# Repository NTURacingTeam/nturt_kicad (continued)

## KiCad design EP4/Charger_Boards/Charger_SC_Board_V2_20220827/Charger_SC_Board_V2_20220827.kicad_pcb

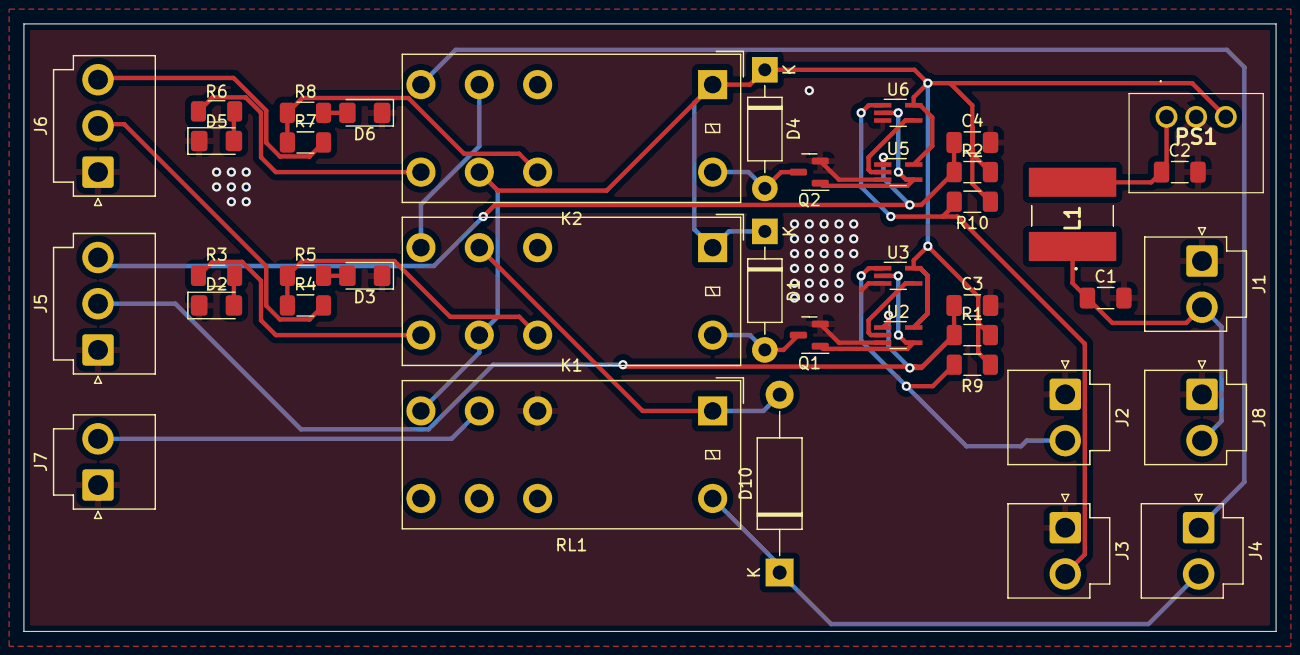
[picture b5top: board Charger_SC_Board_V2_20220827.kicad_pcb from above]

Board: 2 copper layers, 107.3 x 52.1 mm, 40 parts (0 on the bottom side), 29 nets.

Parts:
C1, C3, C4: 10u; C_1206_3216Metric_Pad1.33x1.80mm_HandSolder
C2: 2.2u; C_1206_3216Metric_Pad1.33x1.80mm_HandSolder
D1, D4: 1N4001; D_DO-41_SOD81_P10.16mm_Horizontal
D2, D5: GREEN; D_1206_3216Metric_Pad1.42x1.75mm_HandSolder
D3, D6: RED; D_1206_3216Metric_Pad1.42x1.75mm_HandSolder
D10: D_TVS; D_DO-15_P15.24mm_Horizontal
J1: PWR; JST_VH_B2P-VH-B_1x02_P3.96mm_Vertical
J2: IMD; JST_VH_B2P-VH-B_1x02_P3.96mm_Vertical
J3: BMS; JST_VH_B2P-VH-B_1x02_P3.96mm_Vertical
J4: SC; JST_VH_B2P-VH-B_1x02_P3.96mm_Vertical
J5: Buttons; JST_VH_B3P-VH-B_1x03_P3.96mm_Vertical
J6: Button_LED; JST_VH_B3P-VH-B_1x03_P3.96mm_Vertical
J7: Charger_Control; JST_VH_B2P-VH-B_1x02_P3.96mm_Vertical
J8: HV_PWR; JST_VH_B2P-VH-B_1x02_P3.96mm_Vertical
K1, K2: G2RL-24-DC5; Relay_DPDT_Omron_G2RL
L1: 68u; RLS686
PS1: R-78E5.0-1.0; R78B5020
Q1, Q2: 2N7002; SOT-23
R1, R2, R9, R10: 10K; R_1206_3216Metric_Pad1.30x1.75mm_HandSolder
R3, R5, R6, R8: 680; R_1206_3216Metric_Pad1.30x1.75mm_HandSolder
R4, R7: 100; R_1206_3216Metric_Pad1.30x1.75mm_HandSolder
RL1: G2RL-24-DC5; Relay_DPDT_Omron_G2RL
U2, U3, U5, U6: 74AHC1G00; SOT-353_SC-70-5_Handsoldering

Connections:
+5V: D1.1 (K), D4.1 (K), K1.1, K1.6, K2.1, K2.6, PS1.3 (+VOUT), R1.2, R2.2, R9.1, R10.1, RL1.4, U2.5 (VCC), U3.5 (VCC), U5.5 (VCC), U6.5 (VCC)
+24V: C1.1, J1.2, J8.2, L1.1
/+VCC: C2.1, L1.2, PS1.1 (+VIN)
/BMS_Latch/Latch_Out: Q2.1 (G), U5.4, U6.2
/BMS_Relay_Control/SC_In: K1.4, K2.3
/IMD_Latch/Latch_Out: Q1.1 (G), U2.4, U3.2
BMS_Button: C4.1, J5.3, R2.1, U5.1
BMS_Button_LED: J6.3, R7.2
BMS_Fault: J3.2, R10.2, U6.1
Charger: J7.2, RL1.3
GND: C1.2, C2.2, C3.2, C4.2, D2.1 (K), D3.1 (K), D5.1 (K), D6.1 (K), J1.1, J2.1, J3.1, J5.1, J6.1, J7.1, J8.1, PS1.2 (GND), Q1.2 (S), Q2.2 (S), RL1.2, U2.3 (GND), U3.3 (GND), U5.3 (GND), U6.3 (GND)
IMD_Button: C3.1, J5.2, R1.1, U2.1
IMD_Button_LED: J6.2, R4.2
IMD_Fault: J2.2, R9.2, U3.1
unnamed: D1.2 (A), K1.8, Q1.3 (D)
unnamed: D2.2 (A), R3.2
unnamed: D3.2 (A), R5.2
unnamed: D4.2 (A), K2.8, Q2.3 (D)
unnamed: D5.2 (A), R6.2
unnamed: D6.2 (A), R8.2
unnamed: K1.5, R3.1
unnamed: K1.7, R4.1, R5.1
unnamed: K2.5, R6.1
unnamed: K2.7, R7.1, R8.1
unnamed: U2.2, U3.4
unnamed: U5.2, U6.4
SC_In: D10.1 (A1), J4.2, RL1.8
SC_Out: J4.1, K2.4
SC_Relay_Out: D10.2 (A2), K1.3, RL1.1

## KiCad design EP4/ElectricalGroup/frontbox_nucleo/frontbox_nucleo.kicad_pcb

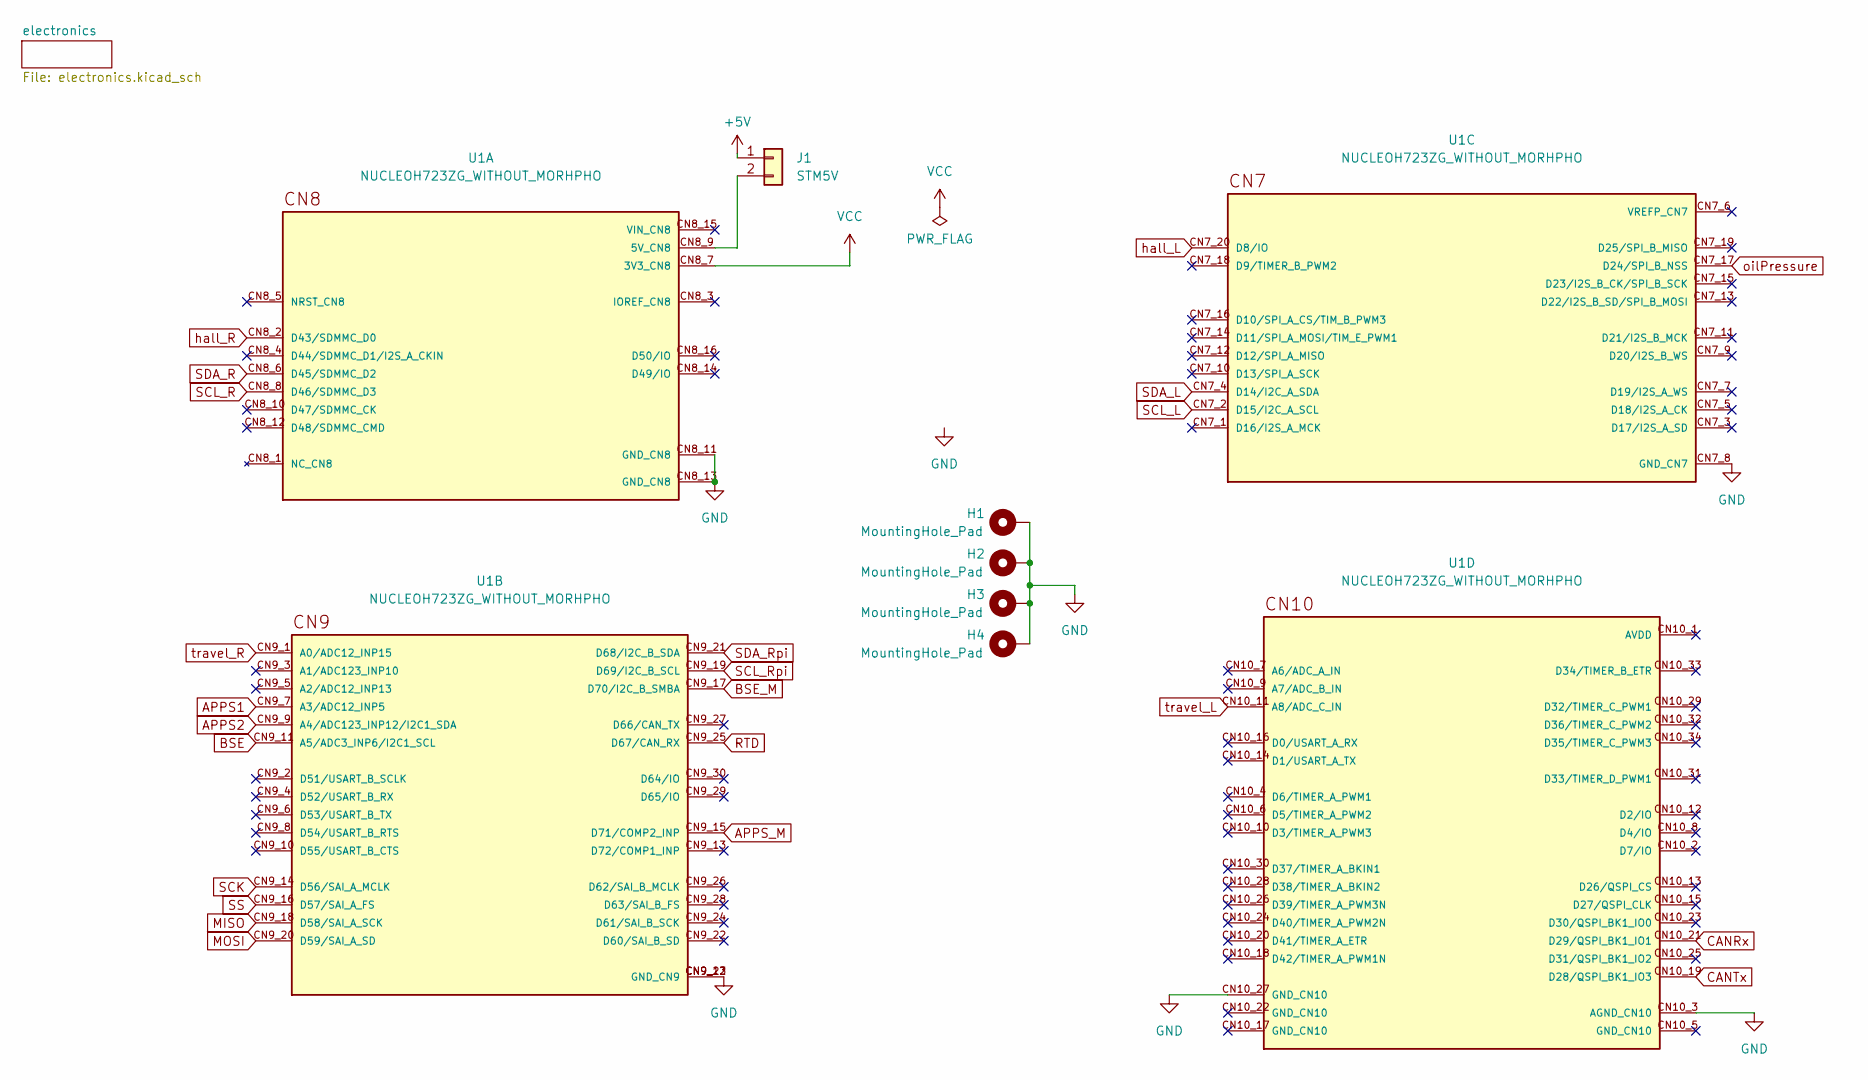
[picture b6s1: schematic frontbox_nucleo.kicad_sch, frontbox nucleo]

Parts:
H1, H2, H3, H4: MountingHole_Pad; MountingHole_2.2mm_M2_DIN965_Pad
J1: STM5V; PinHeader_1x02_P2.54mm_Vertical
U1: NUCLEOH723ZG_WITHOUT_MORHPHO; MODULE_NUCLEOH723ZG_WITHOUT_MORHPHO; PARTREV 2

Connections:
+5V: J1.1; also elsewhere on the board
APPS1: U1.CN9_7 (A3/ADC12_INP5); also elsewhere on the board
APPS2: U1.CN9_9 (A4/ADC123_INP12/I2C1_SDA); also elsewhere on the board
APPS_M: U1.CN9_15 (D71/COMP2_INP); also elsewhere on the board
BSE: U1.CN9_11 (A5/ADC3_INP6/I2C1_SCL); also elsewhere on the board
BSE_M: U1.CN9_17 (D70/I2C_B_SMBA); also elsewhere on the board
CANRx: U1.CN10_21 (D29/QSPI_BK1_IO1); also elsewhere on the board
CANTx: U1.CN10_19 (D28/QSPI_BK1_IO3); also elsewhere on the board
GND: H1.1, H2.1, H3.1, H4.1, U1.CN7_8 (GND_CN7), U1.CN8_11 (GND_CN8), U1.CN8_13 (GND_CN8), U1.CN9_12 (GND_CN9), U1.CN9_23 (GND_CN9), U1.CN10_3 (AGND_CN10), U1.CN10_27 (GND_CN10); also elsewhere on the board
MISO: U1.CN9_18 (D58/SAI_A_SCK); also elsewhere on the board
MOSI: U1.CN9_20 (D59/SAI_A_SD); also elsewhere on the board
unnamed: J1.2, U1.CN8_9 (5V_CN8)
RTD: U1.CN9_25 (D67/CAN_RX); also elsewhere on the board
SCK: U1.CN9_14 (D56/SAI_A_MCLK); also elsewhere on the board
SCL_L: U1.CN7_2 (D15/I2C_A_SCL); also elsewhere on the board
SCL_R: U1.CN8_8 (D46/SDMMC_D3); also elsewhere on the board
SCL_Rpi: U1.CN9_19 (D69/I2C_B_SCL); also elsewhere on the board
SDA_L: U1.CN7_4 (D14/I2C_A_SDA); also elsewhere on the board
SDA_R: U1.CN8_6 (D45/SDMMC_D2); also elsewhere on the board
SDA_Rpi: U1.CN9_21 (D68/I2C_B_SDA); also elsewhere on the board
SS: U1.CN9_16 (D57/SAI_A_FS); also elsewhere on the board
VCC: U1.CN8_7 (3V3_CN8); also elsewhere on the board
hall_L: U1.CN7_20 (D8/IO); also elsewhere on the board
hall_R: U1.CN8_2 (D43/SDMMC_D0); also elsewhere on the board
oilPressure: U1.CN7_17 (D24/SPI_B_NSS); also elsewhere on the board
travel_L: U1.CN10_11 (A8/ADC_C_IN); also elsewhere on the board
travel_R: U1.CN9_1 (A0/ADC12_INP15); also elsewhere on the board

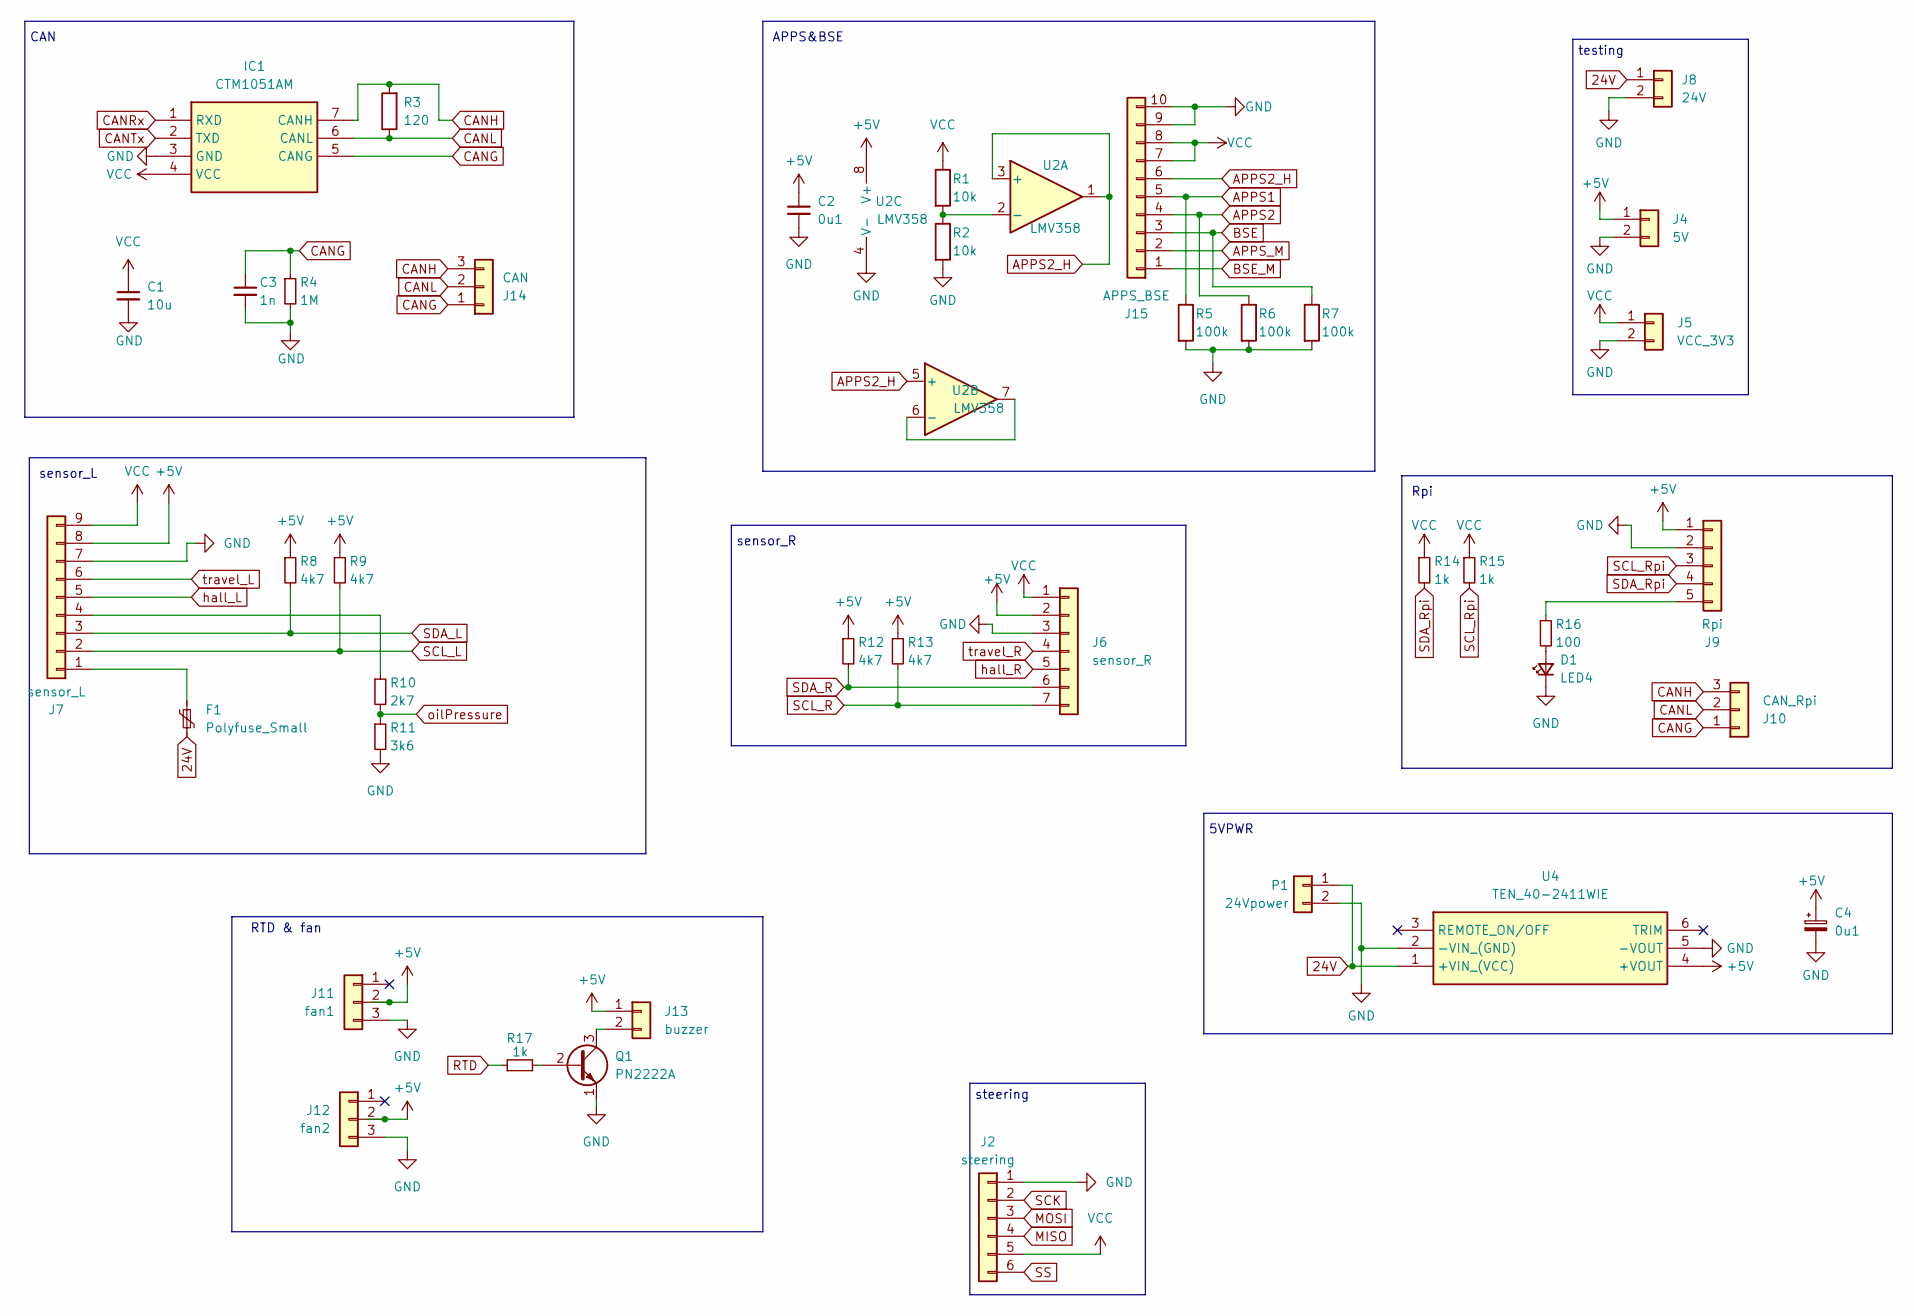
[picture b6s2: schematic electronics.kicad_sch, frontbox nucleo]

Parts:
C1: 10u; C_0805_2012Metric_Pad1.18x1.45mm_HandSolder
C2: 0u1; C_0603_1608Metric
C3: 1n; C_Disc_D5.0mm_W2.5mm_P5.00mm
C4: 0u1; CP_EIA-3528-21_Kemet-B_Pad1.50x2.35mm_HandSolder
D1: LED4; LED_0603_1608Metric_Pad1.05x0.95mm_HandSolder
F1: Polyfuse_Small; Fuse_1206_3216Metric
IC1: CTM1051AM; Manufacturer_Part_Number CTM1051AM
J2: steering; JST_XH_B6B-XH-A_1x06_P2.50mm_Vertical
J4: 5V; PinSocket_1x02_P2.54mm_Vertical
J5: VCC_3V3; PinSocket_1x02_P2.54mm_Vertical
J6: sensor_R; JST_XH_B7B-XH-A_1x07_P2.50mm_Vertical
J7: sensor_L; JST_XH_S9B-XH-A-1_1x09_P2.50mm_Horizontal
J8: 24V; PinSocket_1x02_P2.54mm_Vertical
J9: Rpi; JST_XH_S5B-XH-A-1_1x05_P2.50mm_Horizontal
J10: CAN_Rpi; JST_XH_S3B-XH-A-1_1x03_P2.50mm_Horizontal
J11: fan1; PinHeader_1x03_P2.54mm_Vertical
J12: fan2; PinHeader_1x03_P2.54mm_Vertical
J13: buzzer; JST_XH_B2B-XH-A_1x02_P2.50mm_Vertical
J14: CAN; JST_XH_S3B-XH-A-1_1x03_P2.50mm_Horizontal
J15: APPS_BSE; JST_XH_B10B-XH-A_1x10_P2.50mm_Vertical
P1: 24Vpower; JST_XH_B2B-XH-A_1x02_P2.50mm_Vertical
Q1: PN2222A; TO-92_Inline
R1, R2: 10k; R_0603_1608Metric
R3: 120; R_1206_3216Metric
R4: 1M; R_0603_1608Metric
R5, R6, R7: 100k; R_0603_1608Metric
R8, R9, R12, R13: 4k7; R_0603_1608Metric
R10: 2k7; R_0603_1608Metric
R11: 3k6; R_0603_1608Metric
R14, R15, R17: 1k; R_0603_1608Metric
R16: 100; R_0603_1608Metric
U2: LMV358; SOIC-8_3.9x4.9mm_P1.27mm
U4: TEN_40-2411WIE; TEN402411WIE; Mouser Part Number 495-TEN40-2411WIE

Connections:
24V: F1.2, J8.1, P1.1, U4.1 (+VIN_(VCC))
+5V: C2.1, C4.1, J4.1, J6.2, J7.8, J9.1, J11.2, J12.2, J13.1, R8.1, R9.1, R12.1, R13.1, U2.8 (V+), U4.4 (+VOUT); also elsewhere on the board
APPS1: J15.5, R5.1; also elsewhere on the board
APPS2: J15.4, R6.1; also elsewhere on the board
APPS2_H: J15.6, U2.1, U2.3 (+), U2.5 (+)
APPS_M: J15.2; also elsewhere on the board
BSE: J15.3, R7.1; also elsewhere on the board
BSE_M: J15.1; also elsewhere on the board
CANG: C3.1, IC1.5 (CANG), J10.1, J14.1, R4.1
CANH: IC1.7 (CANH), J10.3, J14.3, R3.2
CANL: IC1.6 (CANL), J10.2, J14.2, R3.1
CANRx: IC1.1 (RXD); also elsewhere on the board
CANTx: IC1.2 (TXD); also elsewhere on the board
GND: C1.2, C2.2, C3.2, C4.2, D1.1 (K), IC1.3 (GND), J2.1, J4.2, J5.2, J6.3, J7.7, J8.2, J9.2, J11.3, J12.3, J15.9, J15.10, P1.2, Q1.1 (E), R2.2, R4.2, R5.2, R6.2, R7.2, R11.2, U2.4 (V-), U4.2 (-VIN_(GND)), U4.5 (-VOUT); also elsewhere on the board
MISO: J2.4; also elsewhere on the board
MOSI: J2.3; also elsewhere on the board
unnamed: D1.2 (A), R16.2
unnamed: F1.1, J7.1
unnamed: J7.4, R10.1
unnamed: J9.5, R16.1
unnamed: J13.2, Q1.3 (C)
unnamed: Q1.2 (B), R17.2
unnamed: R1.2, R2.1, U2.2 (-)
unnamed: U2.6 (-), U2.7
RTD: R17.1; also elsewhere on the board
SCK: J2.2; also elsewhere on the board
SCL_L: J7.2, R9.2; also elsewhere on the board
SCL_R: J6.7, R13.2; also elsewhere on the board
SCL_Rpi: J9.3, R15.2; also elsewhere on the board
SDA_L: J7.3, R8.2; also elsewhere on the board
SDA_R: J6.6, R12.2; also elsewhere on the board
SDA_Rpi: J9.4, R14.2; also elsewhere on the board
SS: J2.6; also elsewhere on the board
VCC: C1.1, IC1.4 (VCC), J2.5, J5.1, J6.1, J7.9, J15.7, J15.8, R1.1, R14.1, R15.1; also elsewhere on the board
hall_L: J7.5; also elsewhere on the board
hall_R: J6.5; also elsewhere on the board
oilPressure: R10.2, R11.1; also elsewhere on the board
travel_L: J7.6; also elsewhere on the board
travel_R: J6.4; also elsewhere on the board

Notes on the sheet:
steering
CAN
sensor_R
RTD & fan
Rpi
testing
5VPWR
APPS&BSE
sensor_L

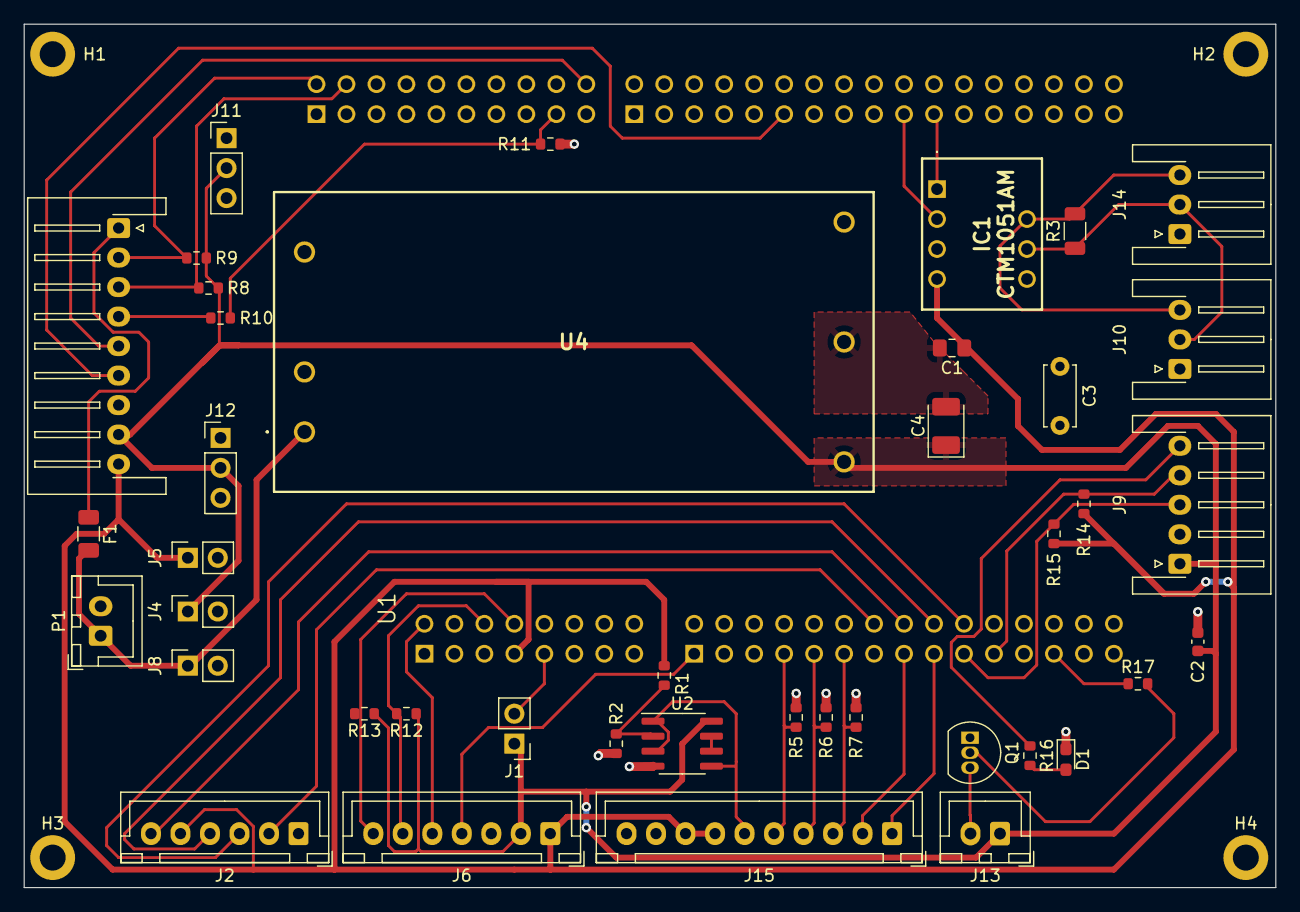
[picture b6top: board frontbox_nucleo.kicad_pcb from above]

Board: 2 copper layers, 106.0 x 73.2 mm, 47 parts (1 on the bottom side), 40 nets.

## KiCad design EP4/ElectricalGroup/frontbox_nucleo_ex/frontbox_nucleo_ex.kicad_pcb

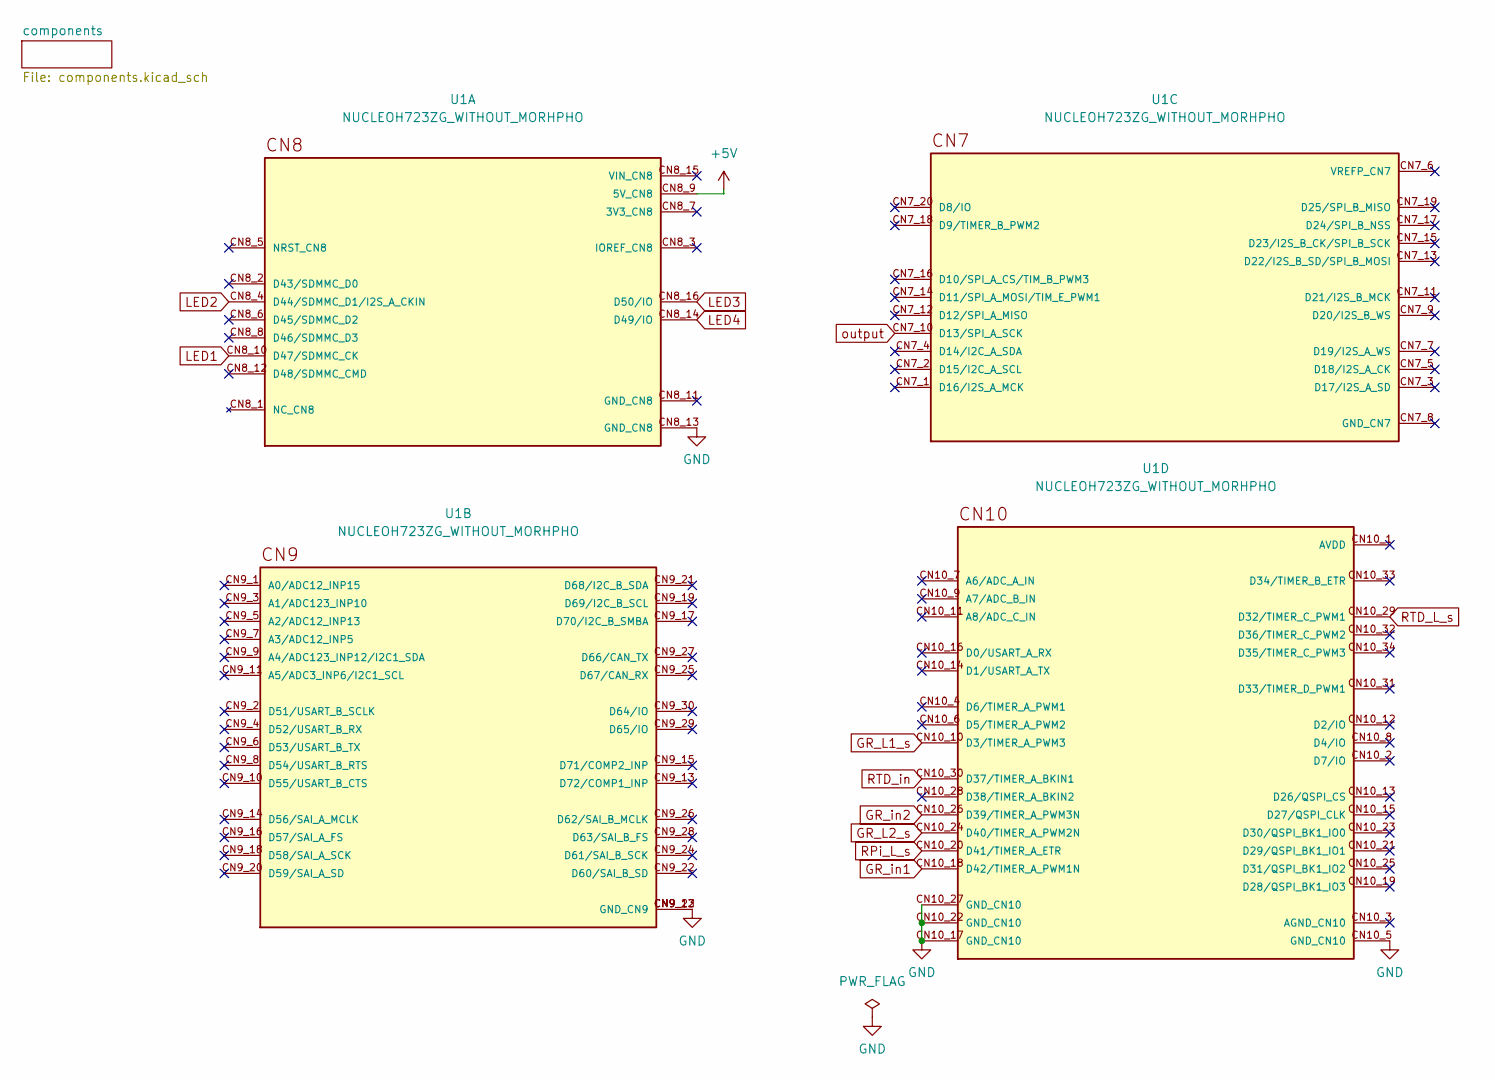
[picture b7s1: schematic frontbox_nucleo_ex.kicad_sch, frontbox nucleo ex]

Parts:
U1: NUCLEOH723ZG_WITHOUT_MORHPHO; MODULE_NUCLEOH723ZG_WITHOUT_MORHPHO; PARTREV 2

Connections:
+5V: U1.CN8_9 (5V_CN8); also elsewhere on the board
GND: U1.CN8_13 (GND_CN8), U1.CN9_12 (GND_CN9), U1.CN9_23 (GND_CN9), U1.CN10_5 (GND_CN10), U1.CN10_17 (GND_CN10), U1.CN10_22 (GND_CN10), U1.CN10_27 (GND_CN10); also elsewhere on the board
GR_L1_s: U1.CN10_10 (D3/TIMER_A_PWM3); also elsewhere on the board
GR_L2_s: U1.CN10_24 (D40/TIMER_A_PWM2N); also elsewhere on the board
GR_in1: U1.CN10_18 (D42/TIMER_A_PWM1N); also elsewhere on the board
GR_in2: U1.CN10_26 (D39/TIMER_A_PWM3N); also elsewhere on the board
LED1: U1.CN8_10 (D47/SDMMC_CK); also elsewhere on the board
LED2: U1.CN8_4 (D44/SDMMC_D1/I2S_A_CKIN); also elsewhere on the board
LED3: U1.CN8_16 (D50/IO); also elsewhere on the board
LED4: U1.CN8_14 (D49/IO); also elsewhere on the board
RPi_L_s: U1.CN10_20 (D41/TIMER_A_ETR); also elsewhere on the board
RTD_L_s: U1.CN10_29 (D32/TIMER_C_PWM1); also elsewhere on the board
RTD_in: U1.CN10_30 (D37/TIMER_A_BKIN1); also elsewhere on the board
output: U1.CN7_10 (D13/SPI_A_SCK); also elsewhere on the board

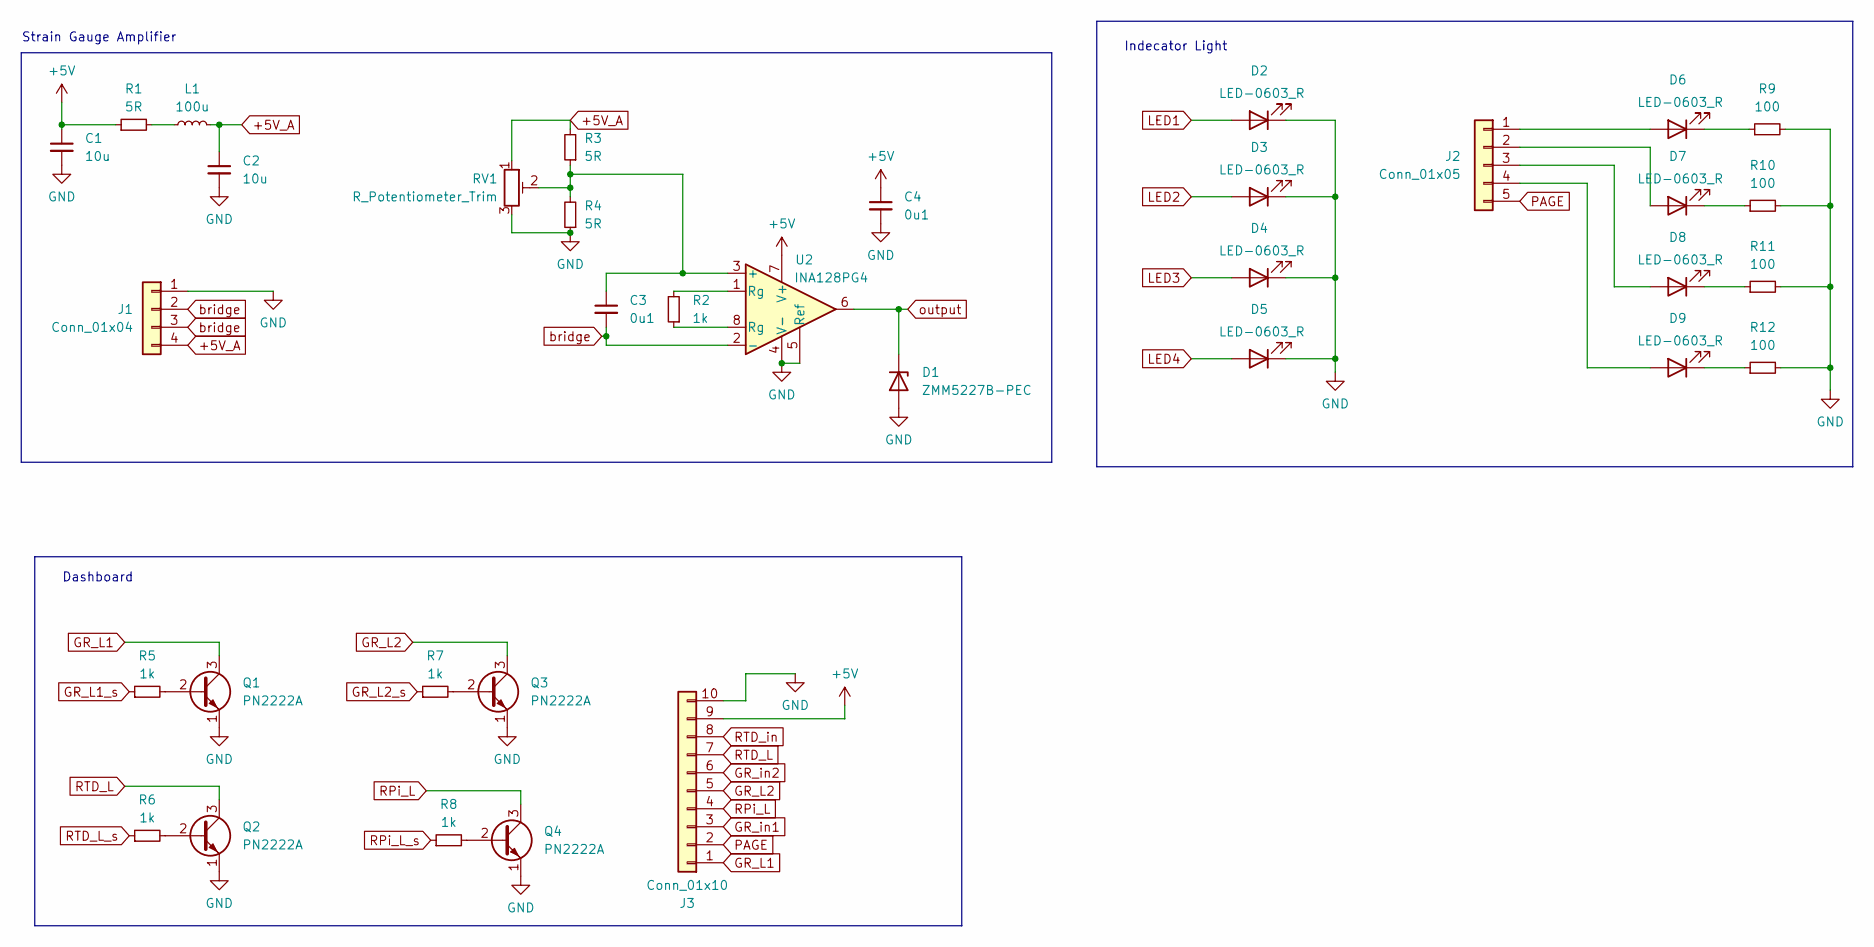
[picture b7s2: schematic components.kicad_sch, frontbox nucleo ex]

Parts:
C1, C2: 10u; C_0603_1608Metric_Pad1.08x0.95mm_HandSolder
C3, C4: 0u1; C_0603_1608Metric_Pad1.08x0.95mm_HandSolder
D1: ZMM5227B-PEC; D_MiniMELF
D2, D3, D4, D5, D6, D7, D8, D9: LED-0603_R; LED_0603_1608Metric_Pad1.05x0.95mm_HandSolder
J1: Conn_01x04; JST_XH_S4B-XH-A_1x04_P2.50mm_Horizontal
J2: Conn_01x05; JST_XH_S5B-XH-A_1x05_P2.50mm_Horizontal
J3: Conn_01x10; JST_XH_S10B-XH-A_1x10_P2.50mm_Horizontal
L1: 100u; L_Axial_L12.0mm_D5.0mm_P15.24mm_Horizontal_Fastron_MISC
Q1, Q2, Q3, Q4: PN2222A; TO-92_Inline
R1, R3, R4: 5R; R_0603_1608Metric_Pad0.98x0.95mm_HandSolder
R2: 1k; R_0805_2012Metric_Pad1.20x1.40mm_HandSolder
R5, R6, R7, R8: 1k; R_0603_1608Metric_Pad0.98x0.95mm_HandSolder
R9, R10, R11, R12: 100; R_0603_1608Metric_Pad0.98x0.95mm_HandSolder
RV1: R_Potentiometer_Trim; Potentiometer_Bourns_3296W_Vertical
U2: INA128PG4; DIP794W53P254L959H508Q8N

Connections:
+5V: C1.1, C4.1, J3.9, R1.1, U2.7 (V+); also elsewhere on the board
+5V_A: C2.1, J1.4, L1.2, R3.2, RV1.1
GND: C1.2, C2.2, C4.2, D1.2 (A), D2.1 (K), D3.1 (K), D4.1 (K), D5.1 (K), J1.1, J3.10, Q1.1 (E), Q2.1 (E), Q3.1 (E), Q4.1 (E), R4.1, R9.2, R10.2, R11.2, R12.2, RV1.3, U2.4 (V-), U2.5 (Ref); also elsewhere on the board
GR_L1: J3.1, Q1.3 (C)
GR_L1_s: R5.1; also elsewhere on the board
GR_L2: J3.5, Q3.3 (C)
GR_L2_s: R7.1; also elsewhere on the board
GR_in1: J3.3; also elsewhere on the board
GR_in2: J3.6; also elsewhere on the board
LED1: D2.2 (A); also elsewhere on the board
LED2: D3.2 (A); also elsewhere on the board
LED3: D4.2 (A); also elsewhere on the board
LED4: D5.2 (A); also elsewhere on the board
unnamed: D6.2 (A), J2.1
unnamed: D6.1 (K), R9.1
unnamed: D7.2 (A), J2.2
unnamed: D7.1 (K), R10.1
unnamed: D8.2 (A), J2.3
unnamed: D8.1 (K), R11.1
unnamed: D9.2 (A), J2.4
unnamed: D9.1 (K), R12.1
unnamed: L1.1, R1.2
unnamed: Q1.2 (B), R5.2
unnamed: Q2.2 (B), R6.2
unnamed: Q3.2 (B), R7.2
unnamed: Q4.2 (B), R8.2
unnamed: R2.1, U2.8 (Rg)
unnamed: R2.2, U2.1 (Rg)
unnamed: C3.1, R3.1, R4.2, RV1.2, U2.3 (+)
PAGE: J2.5, J3.2
RPi_L: J3.4, Q4.3 (C)
RPi_L_s: R8.1; also elsewhere on the board
RTD_L: J3.7, Q2.3 (C)
RTD_L_s: R6.1; also elsewhere on the board
RTD_in: J3.8; also elsewhere on the board
bridge: C3.2, J1.2, J1.3, U2.2 (-)
output: D1.1 (K), U2.6; also elsewhere on the board

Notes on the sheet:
Strain Gauge Amplifier
Indecator Light
Dashboard

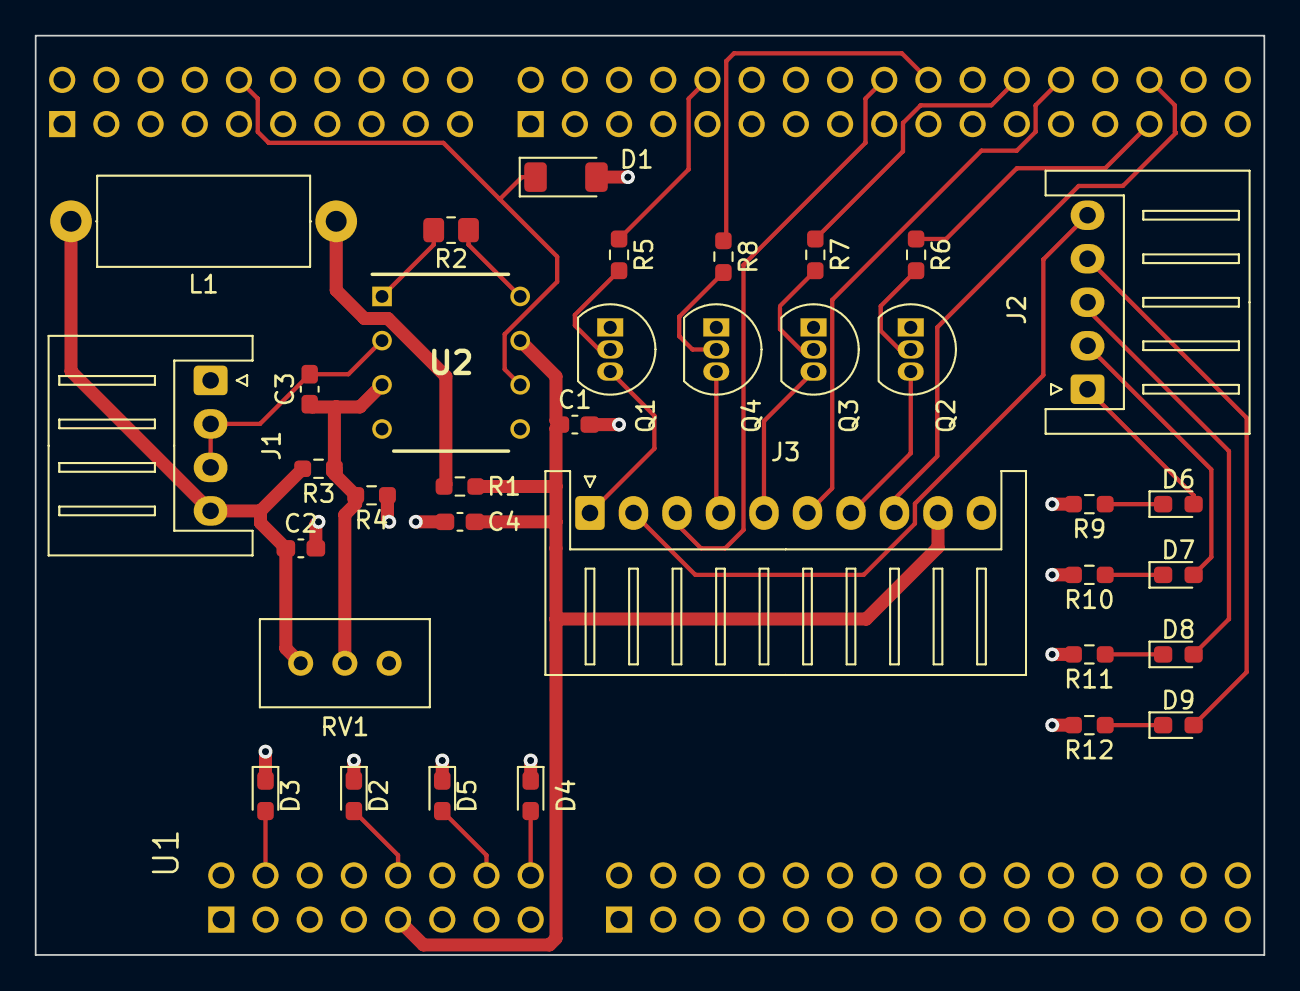
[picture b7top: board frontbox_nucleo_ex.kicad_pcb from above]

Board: 2 copper layers, 70.6 x 52.8 mm, 36 parts (0 on the bottom side), 37 nets.

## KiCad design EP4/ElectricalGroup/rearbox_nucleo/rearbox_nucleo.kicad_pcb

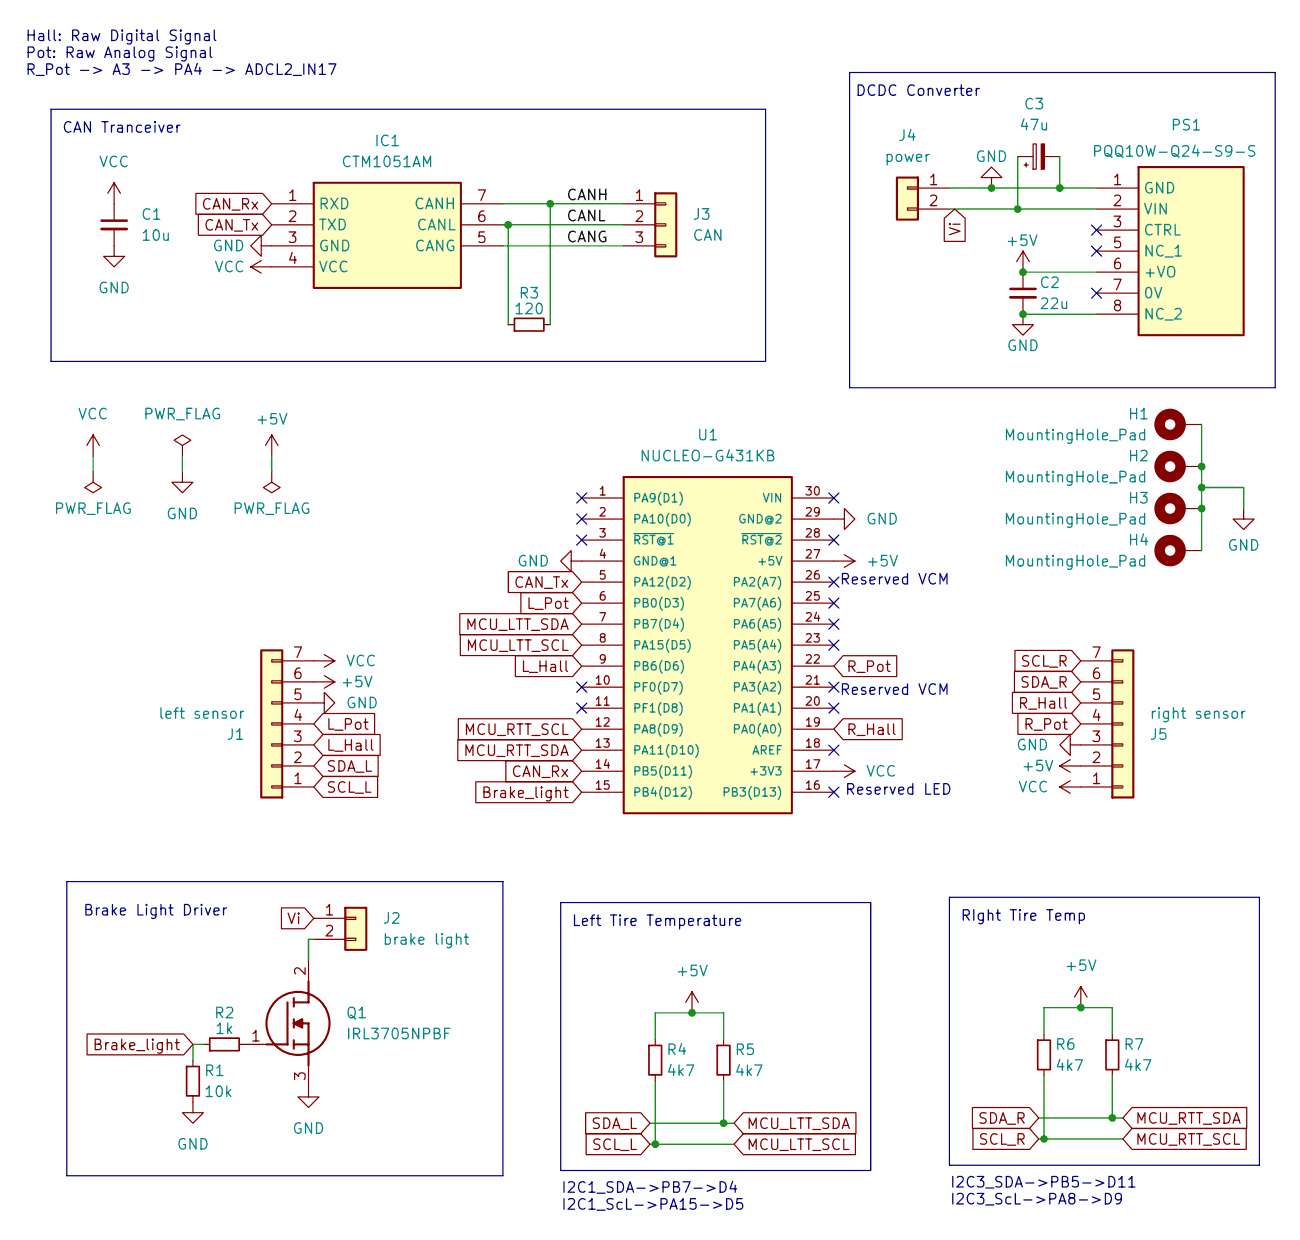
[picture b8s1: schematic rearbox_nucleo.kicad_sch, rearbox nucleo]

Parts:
C1: 10u; C_0805_2012Metric_Pad1.18x1.45mm_HandSolder
C2: 22u; CP_Radial_D6.3mm_P2.50mm
C3: 47u; CP_Radial_Tantal_D6.0mm_P2.50mm
H1, H2, H3, H4: MountingHole_Pad; MountingHole_2.2mm_M2_DIN965_Pad_TopBottom
IC1: CTM1051AM; Manufacturer_Part_Number CTM1051AM
J1: left sensor; JST_XH_B7B-XH-A_1x07_P2.50mm_Vertical
J2: brake light; JST_XH_B2B-XH-A_1x02_P2.50mm_Vertical
J3: CAN; JST_XH_B3B-XH-A_1x03_P2.50mm_Vertical
J4: power; JST_XH_B2B-XH-A_1x02_P2.50mm_Vertical
J5: right sensor; JST_XH_B7B-XH-A_1x07_P2.50mm_Vertical
PS1: PQQ10W-Q24-S9-S; PQQ10WQ24S9S; Manufacturer_Part_Number PQQ10W-Q24-S9-S
Q1: IRL3705NPBF; TO254P469X1042X1930-3P; Manufacturer_Part_Number IRL3705NPBF; Mouser Part Number 942-IRL3705NPBF
R1: 10k; R_0603_1608Metric_Pad0.98x0.95mm_HandSolder
R2: 1k; R_0603_1608Metric_Pad0.98x0.95mm_HandSolder
R3: 120; R_1206_3216Metric_Pad1.30x1.75mm_HandSolder
R4, R5, R6, R7: 4k7; R_0603_1608Metric_Pad0.98x0.95mm_HandSolder
U1: NUCLEO-G431KB; MANUFACTURER_PART_NUMBER NUCLEO-F303K8

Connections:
+5V: C2.1, J1.6, J5.2, PS1.6 (+VO), R4.1, R5.1, R6.1, R7.1, U1.27 (+5V)
/CANG: IC1.5 (CANG), J3.3
/CANH: IC1.7 (CANH), J3.1, R3.2
/CANL: IC1.6 (CANL), J3.2, R3.1
Brake_light: R1.1, R2.1, U1.15 (PB4(D12))
CAN_Rx: IC1.1 (RXD), U1.14 (PB5(D11))
CAN_Tx: IC1.2 (TXD), U1.5 (PA12(D2))
GND: C1.2, C2.2, C3.2, H1.1, H2.1, H3.1, H4.1, IC1.3 (GND), J1.5, J4.1, J5.3, PS1.1 (GND), PS1.8 (NC_2), Q1.3 (S), R1.2, U1.4 (GND@1), U1.29 (GND@2)
L_Hall: J1.3, U1.9 (PB6(D6))
L_Pot: J1.4, U1.6 (PB0(D3))
MCU_LTT_SCL: J1.1, R4.2, U1.8 (PA15(D5))
MCU_LTT_SDA: J1.2, R5.2, U1.7 (PB7(D4))
MCU_RTT_SCL: J5.7, R6.2, U1.12 (PA8(D9))
MCU_RTT_SDA: J5.6, R7.2, U1.13 (PA11(D10))
unnamed: J2.2, Q1.2 (D)
unnamed: Q1.1 (G), R2.2
R_Hall: J5.5, U1.19 (PA0(A0))
R_Pot: J5.4, U1.22 (PA4(A3))
VCC: C1.1, IC1.4 (VCC), J1.7, J5.1, U1.17 (+3V3)
Vi: C3.1, J2.1, J4.2, PS1.2 (VIN)

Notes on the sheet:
RIght Tire Temp
Brake Light Driver
I2C3_SDA->PB5->D11 I2C3_ScL->PA8->D9
Reserved VCM
Reserved LED
Left Tire Temperature
I2C1_SDA->PB7->D4 I2C1_ScL->PA15->D5
CAN Tranceiver
Hall: Raw Digital Signal Pot: Raw Analog Signal R_Pot -> A3 -> PA4 -> ADCL2_IN17
DCDC Converter

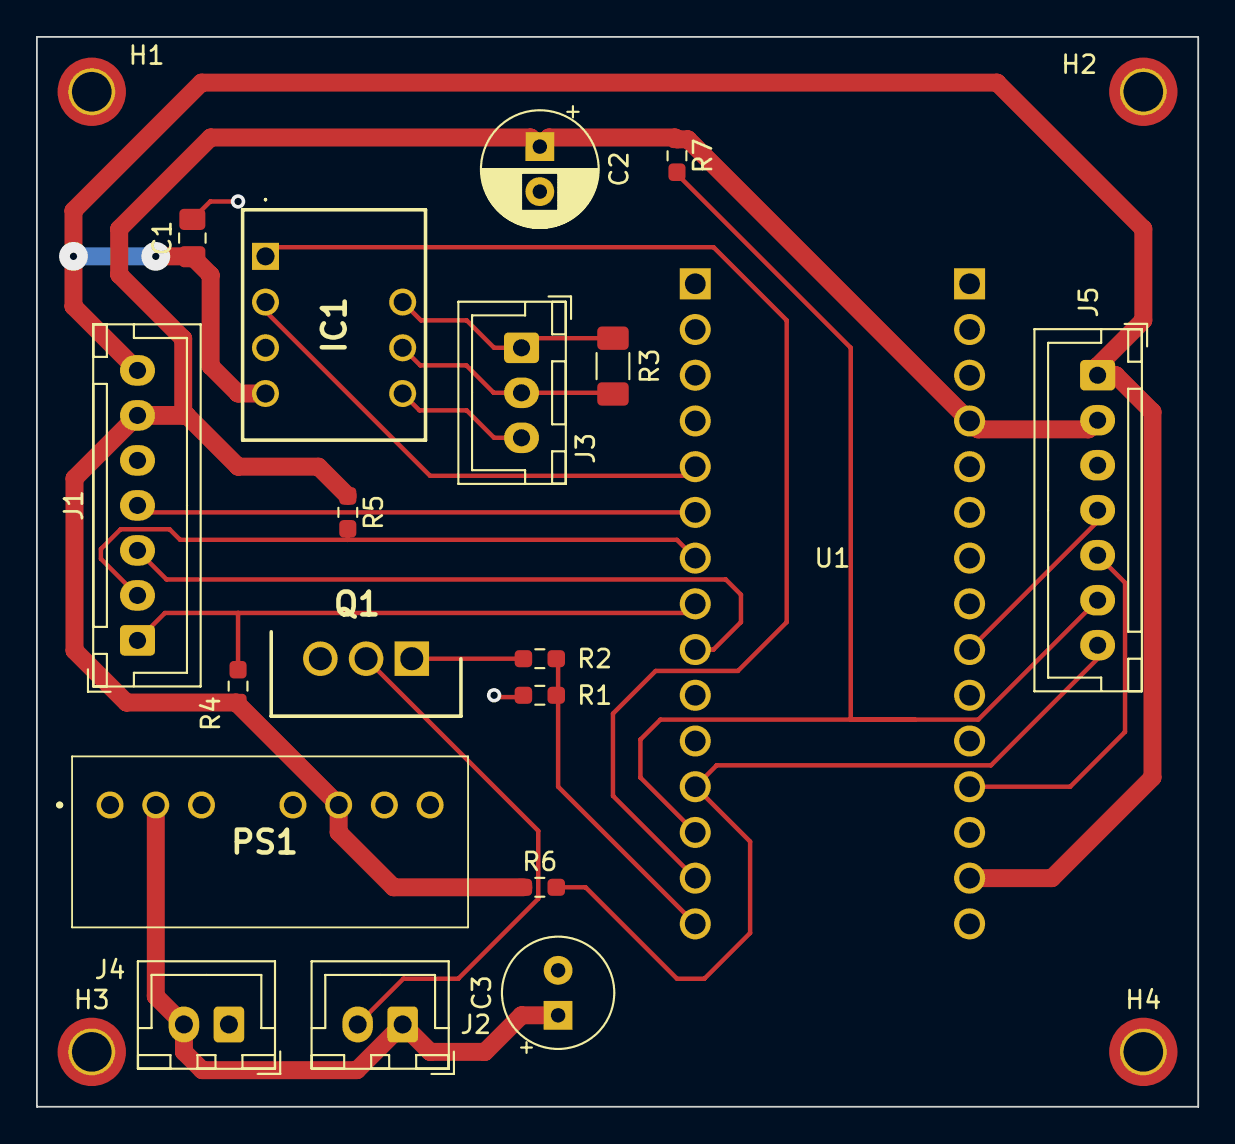
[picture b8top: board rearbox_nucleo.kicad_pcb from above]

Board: 2 copper layers, 64.5 x 59.4 mm, 23 parts (0 on the bottom side), 20 nets.
